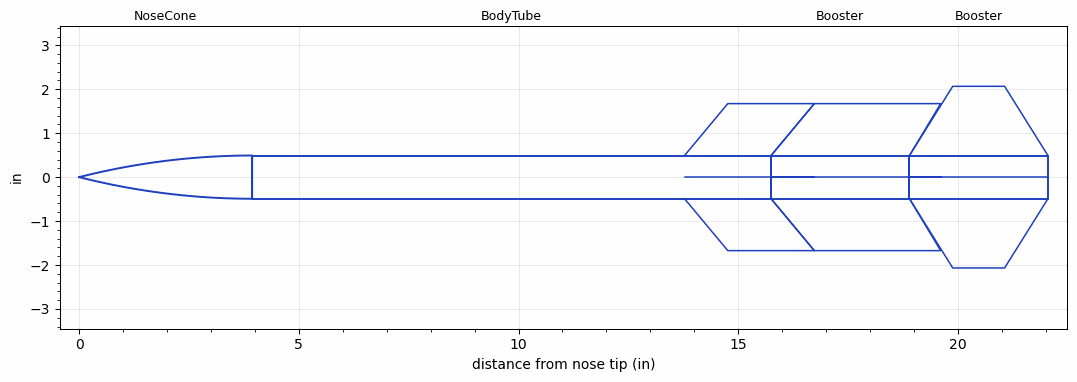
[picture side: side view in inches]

<RASAeroDocument>
 <FileVersion>2</FileVersion>
 <RocketDesign>
  <NoseCone>
   <Length>3.937</Length>
   <Diameter>0.984</Diameter>
   <Shape>Tangent Ogive</Shape>
   <Location>0</Location>
  </NoseCone>
  <BodyTube>
   <Length>11.811</Length>
   <Diameter>0.984</Diameter>
   <Location>3.937</Location>
   <Fin>
    <Count>4</Count>
    <Chord>1.969</Chord>
    <Span>1.181</Span>
    <SweepDistance>0.984</SweepDistance>
    <TipChord>1.969</TipChord>
    <Thickness>0.079</Thickness>
    <Location>1.969</Location>
    <AirfoilSection>Square</AirfoilSection>
   </Fin>
  </BodyTube>
  <Booster>
   <Length>3.15</Length>
   <Diameter>0.984</Diameter>
   <InsideDiameter>0.984</InsideDiameter>
   <Location>15.748</Location>
   <ShoulderLength>0</ShoulderLength>
   <Fin>
    <Count>4</Count>
    <Chord>3.15</Chord>
    <Span>1.181</Span>
    <SweepDistance>0.984</SweepDistance>
    <TipChord>2.875</TipChord>
    <Thickness>0.079</Thickness>
    <Location>3.15</Location>
    <AirfoilSection>Square</AirfoilSection>
   </Fin>
  </Booster>
  <Booster>
   <Length>3.15</Length>
   <Diameter>0.984</Diameter>
   <InsideDiameter>0.984</InsideDiameter>
   <Location>18.898</Location>
   <ShoulderLength>0</ShoulderLength>
   <Fin>
    <Count>4</Count>
    <Chord>3.15</Chord>
    <Span>1.575</Span>
    <SweepDistance>0.984</SweepDistance>
    <TipChord>1.181</TipChord>
    <Thickness>0.079</Thickness>
    <Location>3.15</Location>
    <AirfoilSection>Square</AirfoilSection>
   </Fin>
  </Booster>
  <Surface>Smooth (Zero Roughness)</Surface>
  <ModifiedBarrowman>False</ModifiedBarrowman>
  <Turbulence>False</Turbulence>
  <UseBooster1>False</UseBooster1>
  <UseBooster2>False</UseBooster2>
 </RocketDesign>
 <LaunchSite>
  <Altitude>3750</Altitude>
  <Pressure>0</Pressure>
  <RodAngle>7.64</RodAngle>
  <RodLength>12</RodLength>
  <Temperature>80</Temperature>
  <WindSpeed>0</WindSpeed>
 </LaunchSite>
 <Recovery>
  <Altitude1>1000</Altitude1>
  <Altitude2>1000</Altitude2>
  <DeviceType1>None</DeviceType1>
  <DeviceType2>None</DeviceType2>
  <Event1>False</Event1>
  <Event2>False</Event2>
  <Size1>1</Size1>
  <Size2>1</Size2>
  <EventType1>None</EventType1>
  <EventType2>None</EventType2>
  <CD1>1.33</CD1>
  <CD2>1.33</CD2>
 </Recovery>
</RASAeroDocument>
